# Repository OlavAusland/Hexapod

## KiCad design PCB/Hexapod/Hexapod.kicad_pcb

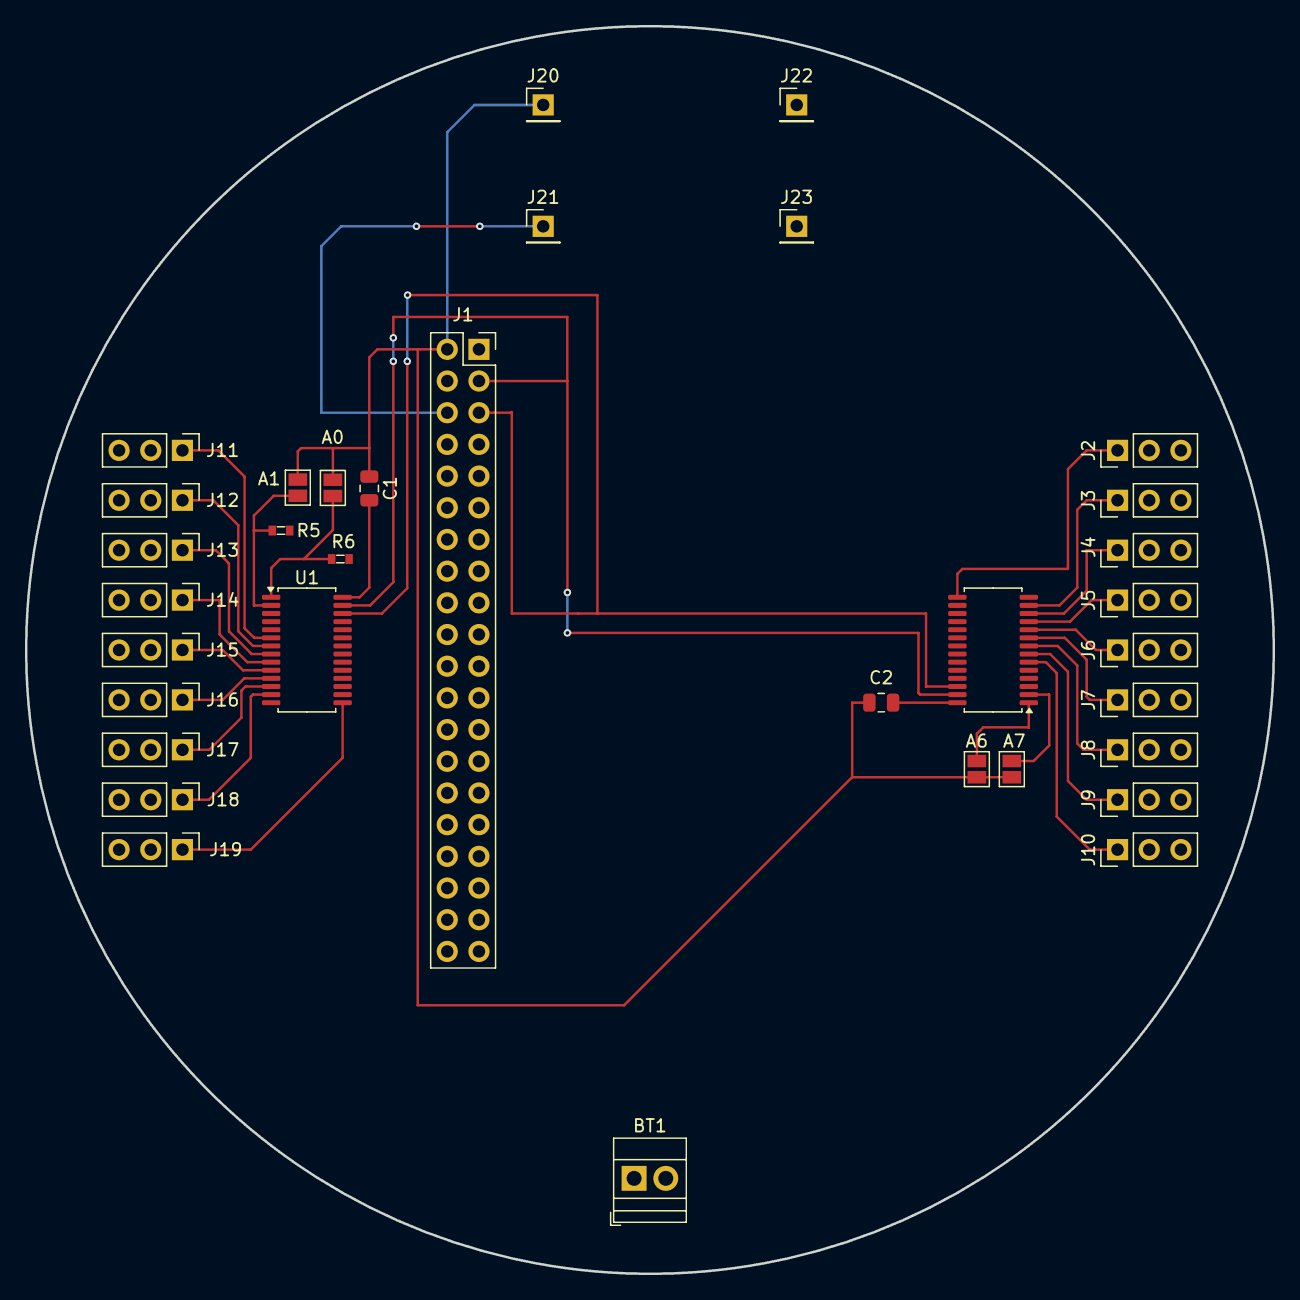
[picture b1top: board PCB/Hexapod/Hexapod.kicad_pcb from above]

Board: 4 copper layers, 100.0 x 100.0 mm, 34 parts (0 on the bottom side), 30 nets.

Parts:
A0, A1, A6, A7: SolderJumper-2_P1.3mm_Open_Pad1.0x1.5mm
BT1: Battery; TerminalBlock_Xinya_XY308-2.54-2P_1x02_P2.54mm_Horizontal
C1, C2: 10uF; C_0805_2012Metric
J1: Raspberry; PinSocket_2x20_P2.54mm_Vertical
J2, J3, J4, J5, J6, J7, J8, J9, J10, J11, J12, J13, J14, J15, J16, J17, J18, J19: PinHeader_1x03_P2.54mm_Vertical
J20, J21, J22, J23: PinHeader_1x01_P2.54mm_Vertical
R5, R6: 10K; 0603
U1, U2: PCA9685PW; TSSOP-28_4.4x9.7mm_P0.65mm

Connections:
5.0V: A0.1 (A), A1.1 (A), A6.1 (A), A7.1 (A), C1.1, C2.1, J1.2, J1.4, J20.1
+BATT: BT1.1 (+), J2.2, J3.2, J4.2, J5.2, J6.2, J7.2, J8.2, J9.2, J10.2, J11.2, J12.2, J13.2, J14.2, J15.2, J16.2, J17.2, J18.2, J19.2, J23.1
-BATT: BT1.2 (-), J2.3, J3.3, J4.3, J5.3, J6.3, J7.3, J8.3, J9.3, J10.3, J11.3, J12.3, J13.3, J14.3, J15.3, J16.3, J17.3, J18.3, J19.3, J22.1, R5.2, R6.2, U1.3 (A2), U1.4 (A3), U1.5 (A4), U1.14 (VSS), U1.24 (A5), U1.25 (EXTCLK), U2.3 (A2), U2.4 (A3), U2.5 (A4), U2.14 (VSS), U2.24 (A5), U2.25 (EXTCLK)
/A0: A0.2 (B), R6.1, U1.1 (A0)
/A1: A1.2 (B), R5.1, U1.2 (A1)
/A6: A6.2 (B), U2.1 (A0)
/A7: A7.2 (B), U2.2 (A1)
/PWM0: J11.1, U1.6 (LED0)
/PWM1: J12.1, U1.7 (LED1)
/PWM2: J13.1, U1.8 (LED2)
/PWM3: J14.1, U1.9 (LED3)
/PWM4: J15.1, U1.10 (LED4)
/PWM5: J16.1, U1.11 (LED5)
/PWM6: J17.1, U1.12 (LED6)
/PWM7: J18.1, U1.13 (LED7)
/PWM8: J19.1, U1.15 (LED8)
/PWM9: J2.1, U2.15 (LED8)
/PWM10: J3.1, U2.13 (LED7)
/PWM11: J4.1, U2.12 (LED6)
/PWM12: J5.1, U2.11 (LED5)
/PWM13: J6.1, U2.10 (LED4)
/PWM14: J7.1, U2.9 (LED3)
/PWM15: J8.1, U2.8 (LED2)
/PWM16: J9.1, U2.7 (LED1)
/PWM17: J10.1, U2.6 (LED0)
/SCL: J1.5, U1.26 (SCL), U2.26 (SCL)
/SDA: J1.3, U1.27 (SDA), U2.27 (SDA)
GND: J1.6, J21.1
unnamed: C1.2, U1.28 (VDD)
unnamed: C2.2, U2.28 (VDD)

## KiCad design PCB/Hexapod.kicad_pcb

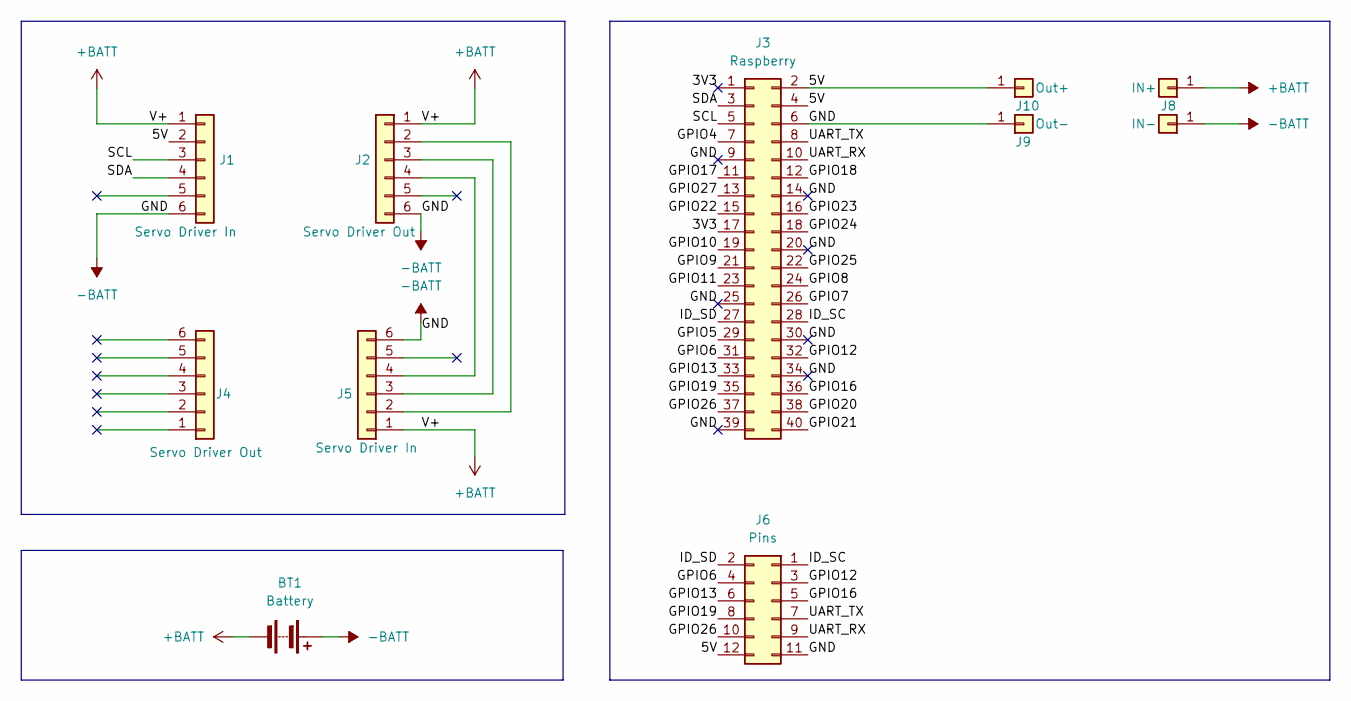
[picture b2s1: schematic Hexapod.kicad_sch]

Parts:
BT1: Battery; AMASS_XT60-F_1x02_P7.20mm_Vertical
J1, J5: Servo Driver In; PinHeader_1x06_P2.00mm_Vertical
J2, J4: Servo Driver Out; PinHeader_1x06_P2.00mm_Vertical
J3: Raspberry; PinSocket_2x20_P2.00mm_Vertical
J6: Pins; PinSocket_2x06_P2.00mm_Vertical
J7: IN-; PinHeader_1x01_P2.00mm_Vertical
J8: IN+; PinHeader_1x01_P2.00mm_Vertical
J9: Out-; PinHeader_1x01_P2.00mm_Vertical
J10: Out+; PinHeader_1x01_P2.00mm_Vertical

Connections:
+BATT: BT1.2 (-), J1.1, J2.1, J5.1, J8.1
-BATT: BT1.1 (+), J1.6, J2.6, J3.6, J3.9, J3.14, J3.20, J3.25, J3.30, J3.34, J3.39, J5.6, J6.11, J7.1, J9.1
/3V3: J3.1, J3.17
/5V: J1.2, J3.2, J3.4, J6.12, J10.1
/GPIO4: J3.7
/GPIO5: J3.29
/GPIO6: J3.31, J6.4
/GPIO7: J3.26
/GPIO8: J3.24
/GPIO9: J3.21
/GPIO10: J3.19
/GPIO11: J3.23
/GPIO12: J3.32, J6.3
/GPIO13: J3.33, J6.6
/GPIO16: J3.36, J6.5
/GPIO17: J3.11
/GPIO18: J3.12
/GPIO19: J3.35, J6.8
/GPIO20: J3.38
/GPIO21: J3.40
/GPIO22: J3.15
/GPIO23: J3.16
/GPIO24: J3.18
/GPIO25: J3.22
/GPIO26: J3.37, J6.10
/GPIO27: J3.13
/ID_SC: J3.28, J6.1
/ID_SD: J3.27, J6.2
/SCL: J1.3, J3.5
/SDA: J1.4, J3.3
/UART_RX: J3.10, J6.9
/UART_TX: J3.8, J6.7
unnamed: J2.2, J5.2
unnamed: J2.3, J5.3
unnamed: J2.4, J5.4

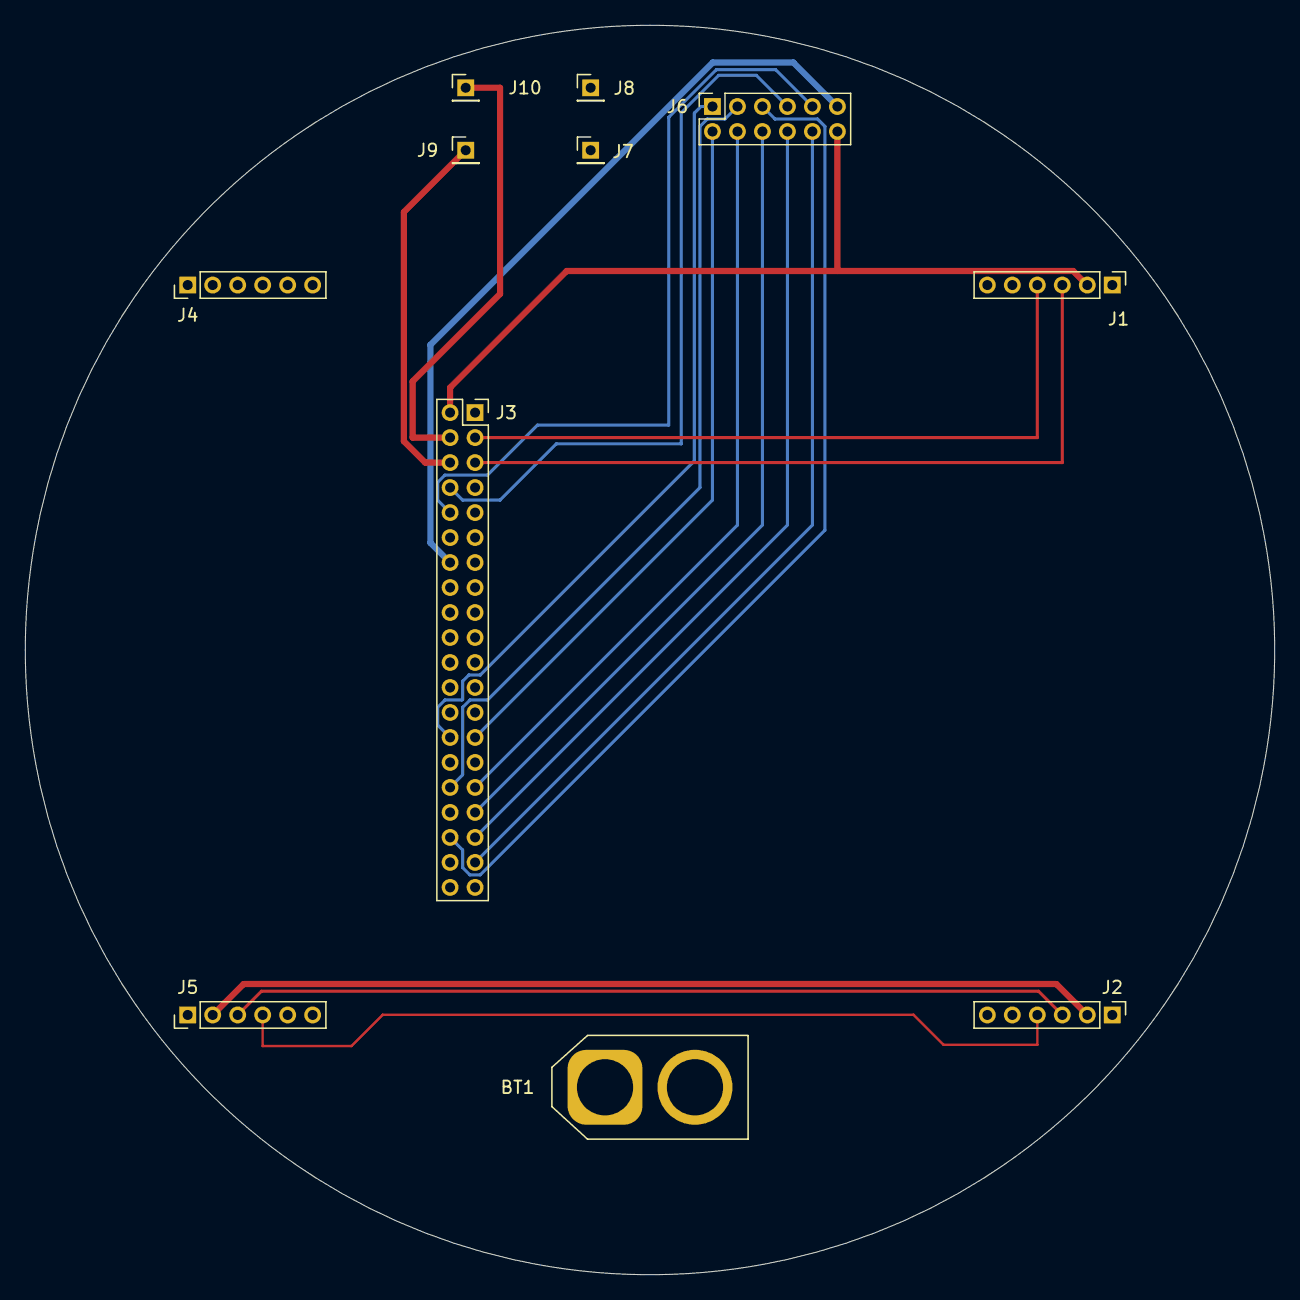
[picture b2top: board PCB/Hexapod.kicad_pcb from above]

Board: 4 copper layers, 100.0 x 100.0 mm, 11 parts (0 on the bottom side), 19 nets.

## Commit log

2024-08-17 Add PCB files
2024-08-19 Update schematic and PCB
2024-08-25 Add Windows UDP library
2024-08-25 Add draft version of Linux UDP support
2024-09-06 Add improved hexapod PCB
2024-10-02 Add simulator base
2025-10-13 Initial commit with current hexapod model ( not finished )
